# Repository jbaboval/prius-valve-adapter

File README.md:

# VintageAir to Prius Heater Valve Adapter

Vintage Air systems ship with a simple on/off heater control valve which stops coolant flow to the heater core when the AC is on. 

Chevy GenV small block engines (L86/LT1, L83, etc) require constant flow through the heater loop, so a simple on/off valve is not suitable.

2nd Generation Toyota Prius' (2004-2009) have an ideal three-way coolant valve that is relatively inexpensive. (Sub-$20), but uses an ECU controlled motor. (Part number 16670-21010)

This adapter connects the Vintage Air one-wire on/off signal to the five-wire Prius valve.

The adapter is based on an ATTiny24, with a DRV8871 motor driver. It is powered by an AP7583AQ voltage regulator, and the input level is shifted from IGN voltage by a PC817C optical coupler.

# Pinout

The Prius valve has a brushed DC motor that turns a ball valve through a worm drive. The valve stem is connected to a simple potentiometer. The motor and potentiometer pins are exposed in the five wire connector:

* Red - Brushed DC Motor
* Black - Brushed DC Motor
* White - Potentiometer Wiper
* Green - Potentiometer +
* Blue - Potentiometer -

The Vintage Air controller has one blue wire that is either N/C or +12v when the AC is on.

One side of the board has labeled pins for the color coded Prius valve wires. The other side takes +12v, GND, and the VintageAir in.

# BOM

| Part Number      | Quantity | Link               |
|------------------|----------|---------------------------|
| ATTiny24A-SSU         | 1        | https://www.digikey.com/en/products/detail/microchip-technology/ATTINY24A-SSU/2050982           |
| DRV8871          | 1        | https://www.digikey.com/en/products/detail/texas-instruments/DRV8871DDAR/5639726          |
| AP7583AQ-50MP-13         | 1        | https://www.digikey.com/en/products/detail/diodes-incorporated/AP7583AQ-50MP-13/17736704        |
| PC817C          | 1        | https://www.amazon.com/dp/B0DJ8ZBHJ2               |
| 1206 10uF Ceramic Capacitor        | 5        |            |
| 1206 0.1uF Ceramic Capacitor | 1 | |
| 22uF/63v Capacitor | 1 | https://www.digikey.com/en/products/detail/kemet/EDK226M063S9HAA/6597717|
| 2010 270ohm 1.25W Resistor | 1| https://www.digikey.com/en/products/detail/te-connectivity-passive-product/CRGP2010F270R/8577255 |
| 1206 10K Resistor | 1| |
| 1206 30K Resistor | 1| |

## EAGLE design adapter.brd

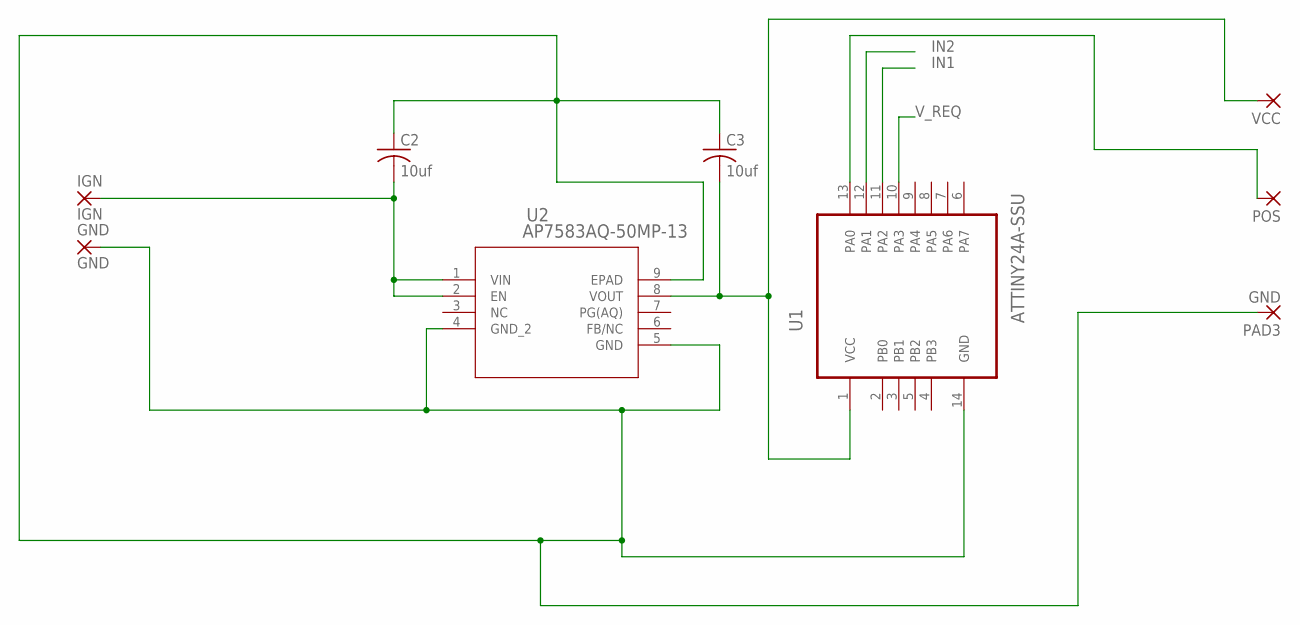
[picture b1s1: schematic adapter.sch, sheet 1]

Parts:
C2, C3: 10uf; C1206
GND: GND; 2,15/1,0
IGN: IGN; 2,15/1,0
PAD3: GND; 2,15/1,0
POS: 2,15/1,0
U1: ATTINY24A-SSU; SOIC127P600X175-14N
U2: AP7583AQ-50MP-13; MSOP-8EP_DIO
VCC: 2,15/1,0

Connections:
GND: C2.1, C3.1, GND.1, PAD3.1, U1.14 (GND), U2.4 (GND_2), U2.5 (GND), U2.9 (EPAD); also elsewhere on the board
IGN: C2.2, IGN.1, U2.1 (VIN), U2.2 (EN); also elsewhere on the board
IN1: U1.11 (PA2); also elsewhere on the board
IN2: U1.12 (PA1); also elsewhere on the board
unnamed: POS.1, U1.13 (PA0)
VCC: C3.2, U1.1 (VCC), U2.8 (VOUT), VCC.1; also elsewhere on the board
V_REQ: U1.10 (PA3); also elsewhere on the board

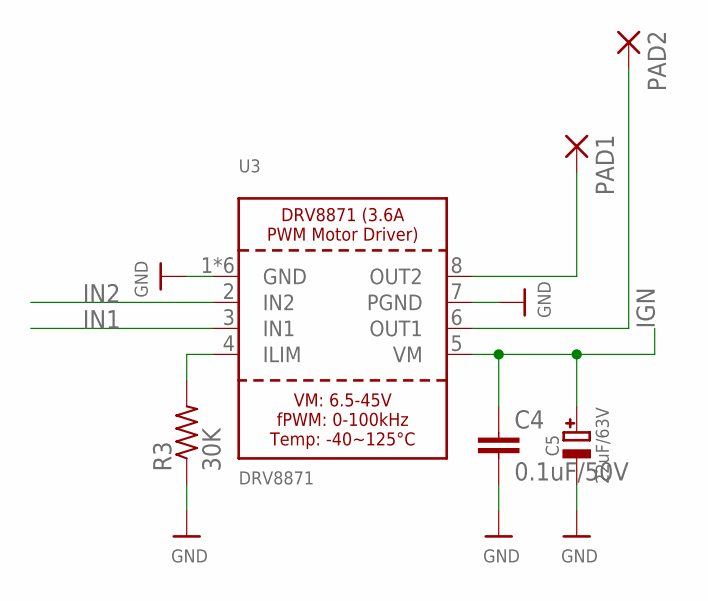
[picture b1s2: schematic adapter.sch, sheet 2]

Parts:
C4: 0.1uF/50V; C1206
C5: 22uF/63V; PANASONIC_D
PAD1, PAD2: 2,15/1,0
R3: 30K; M1206
U3: DRV8871; HSOP8

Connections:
GND: C4.2, C5.-, R3.1, U3.1 (GND), U3.7 (PGND), U3.GND, U3.P$1 (GND), U3.P$2 (GND), U3.P$3 (GND), U3.P$4 (GND); also elsewhere on the board
IGN: C4.1, C5.+, U3.5 (VM); also elsewhere on the board
IN1: U3.3 (IN1); also elsewhere on the board
IN2: U3.2 (IN2); also elsewhere on the board
unnamed: R3.2, U3.4 (ILIM)
OUT1: PAD2.1, U3.6 (OUT1)
OUT2: PAD1.1, U3.8 (OUT2)

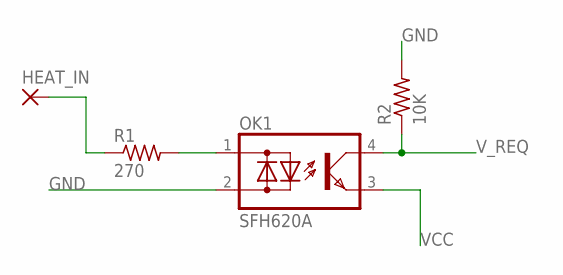
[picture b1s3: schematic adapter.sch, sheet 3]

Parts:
HEAT_IN: 2,15/1,0
OK1: SFH620A; DIL04
R1: 270; R2010
R2: 10K; M1206

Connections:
GND: OK1.2 (AC2), R2.2; also elsewhere on the board
unnamed: OK1.1 (AC1), R1.2
unnamed: HEAT_IN.1, R1.1
VCC: OK1.3 (E); also elsewhere on the board
V_REQ: OK1.4 (C), R2.1; also elsewhere on the board

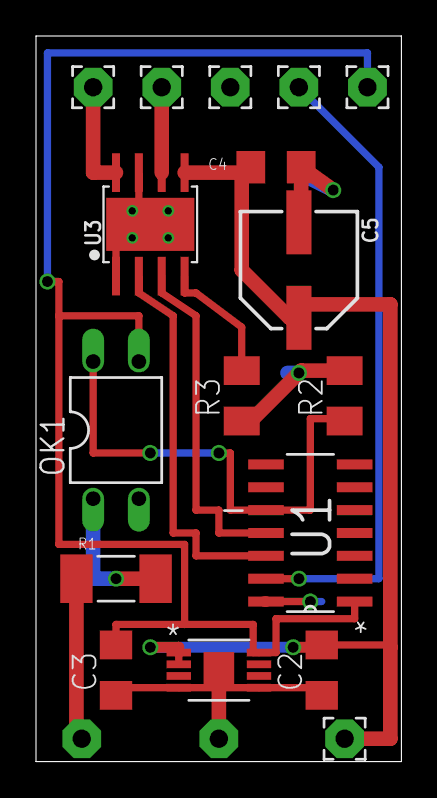
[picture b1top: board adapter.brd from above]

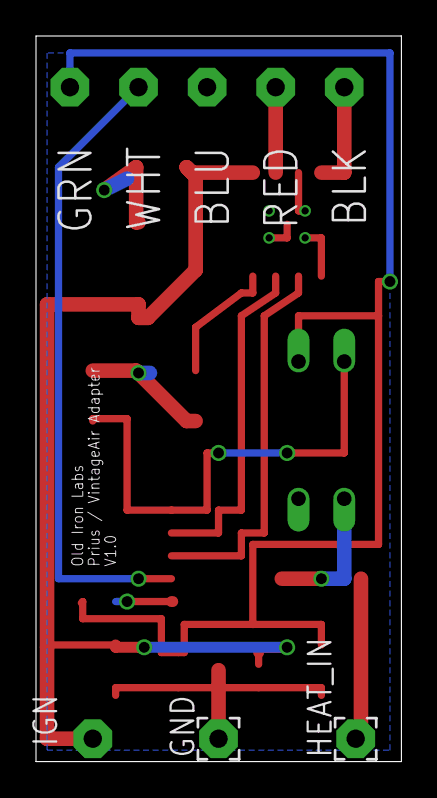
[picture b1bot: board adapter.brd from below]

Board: 2 copper layers, 20.3 x 40.3 mm, 19 parts (2 on the bottom side), 12 nets.

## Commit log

2025-09-28 Add README
2025-09-28 Add LICENSE
2025-09-28 Add valve part number

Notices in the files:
parts and their libraries:
microbuilder: This work is placed in the public domain, and may be freely used for commercial and non-commercial work with the following conditions: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
COPYRIGHT: Copyright (C) 2024 Ultra Librarian. All rights reserved.
